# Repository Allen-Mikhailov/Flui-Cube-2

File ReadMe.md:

# An attempt to make a small cube that can simulate a fluid simulation on some led matricies

Using 788BS matrix for lights

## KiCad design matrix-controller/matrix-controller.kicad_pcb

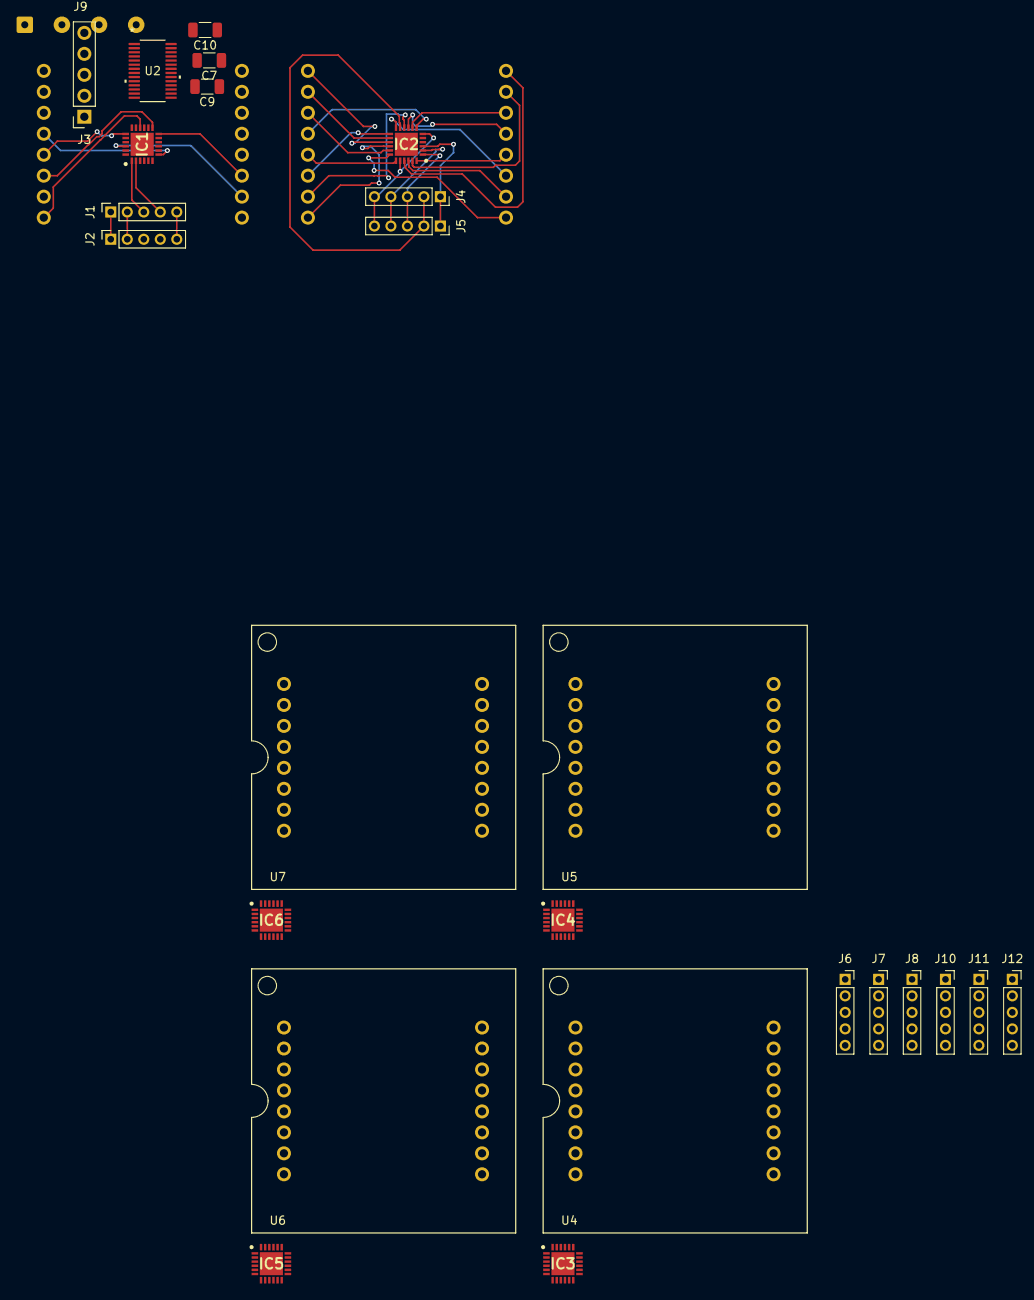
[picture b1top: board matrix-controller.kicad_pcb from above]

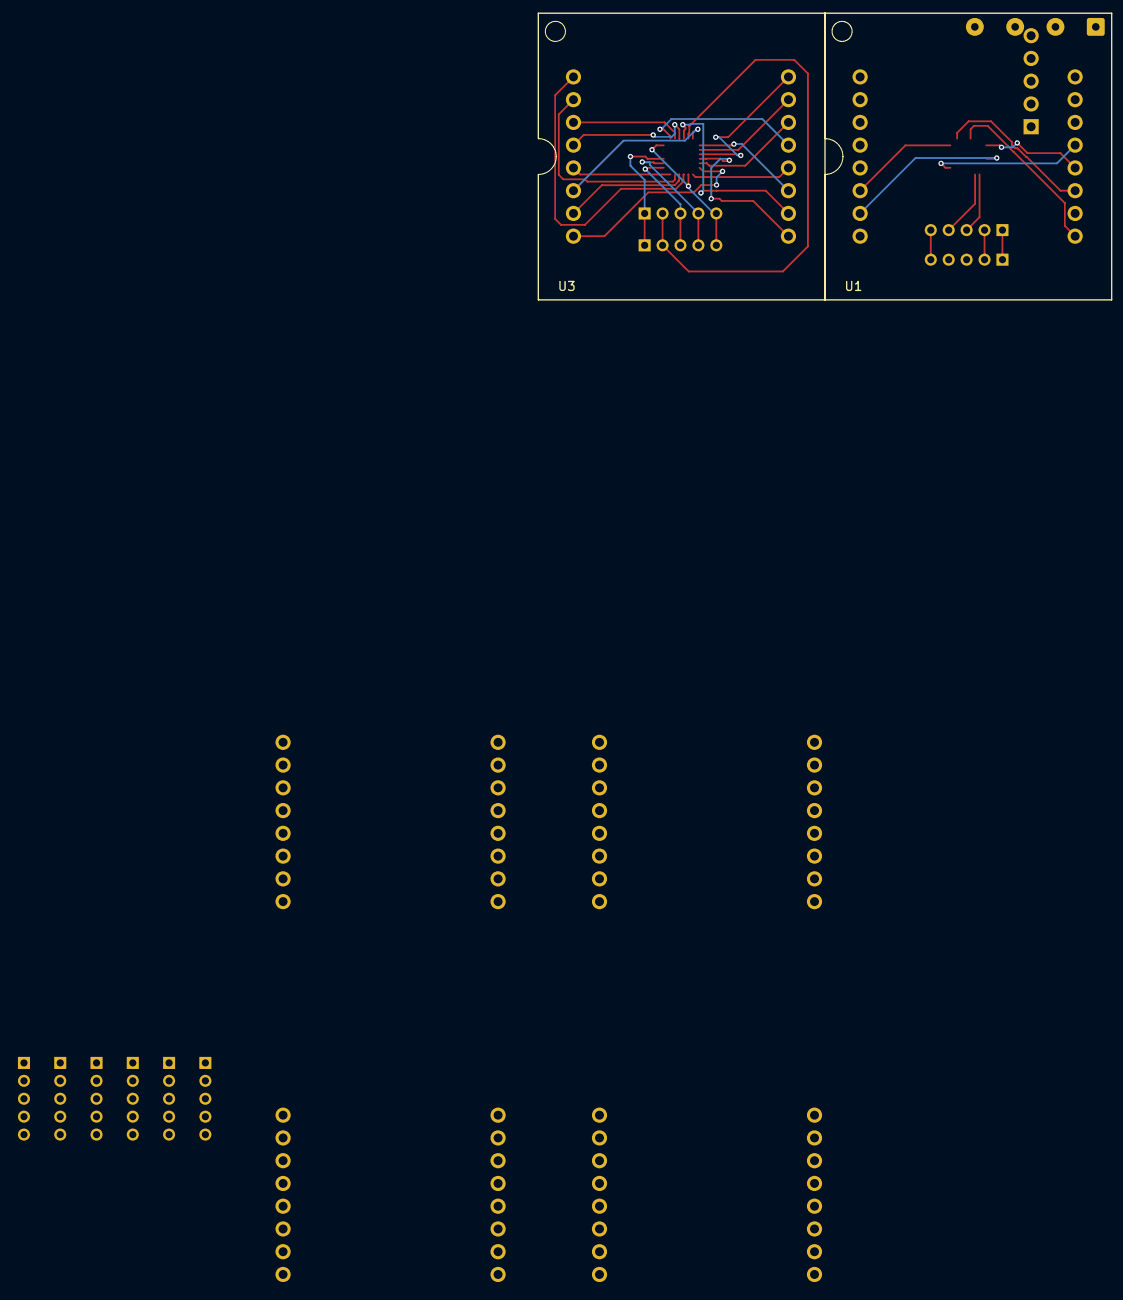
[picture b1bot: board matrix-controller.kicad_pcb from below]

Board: 2 copper layers, 28 parts (2 on the bottom side), 118 nets.

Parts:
C7: 10uF; C_1206_3216Metric
C9: 0.1uF; C_1206_3216Metric
C10: 0.47uF; C_1206_3216Metric
IC1, IC2, IC3, IC4, IC5, IC6: IS31FL3728-QFLS2-TR; QFN50P400X400X80-25N-D
J1: 1x05_Socket_Front; PinSocket_1x05_P2.00mm_Vertical
J2: 1x05_Socket_Back; PinSocket_1x05_P2.00mm_Vertical
J3: Conn_01x05_Pin; PinSocket_1x05_P2.54mm_Vertical
J4: 1x05_Socket_Front_Input; PinSocket_1x05_P2.00mm_Vertical
J5, J7: 1x05_Socket_Left; PinSocket_1x05_P2.00mm_Vertical
J6: 1x05_Socket_Left_Input; PinSocket_1x05_P2.00mm_Vertical
J8: 1x05_Socket_Top_Input; PinSocket_1x05_P2.00mm_Vertical
J9: Conn_01x04_Pin; SolderWire-0.25sqmm_1x04_P4.5mm_D0.65mm_OD2mm
J10: 1x05_SocketBack_Input; PinSocket_1x05_P2.00mm_Vertical
J11: 1x05_Socket_Right; PinSocket_1x05_P2.00mm_Vertical
J12: 1x05_Socket_Right_Input; PinSocket_1x05_P2.00mm_Vertical
U1, U3, U4, U5, U6, U7: 1088BS; LED_1088
U2: XMSM0G3507SDGS28R; VSSOP28_DGS_TEX

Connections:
/MatrixPlusDriver1/C1: IC2.24 (C1), U3.5 (C1)
/MatrixPlusDriver1/C2: IC2.23 (C2), U3.2 (C2)
/MatrixPlusDriver1/C3: IC2.22 (C3), U3.7 (C3)
/MatrixPlusDriver1/C4: IC2.21 (C4), U3.1 (C4)
/MatrixPlusDriver1/C5: IC2.19 (C5), U3.12 (C5)
/MatrixPlusDriver1/C6: IC2.18 (C6), U3.8 (C6)
/MatrixPlusDriver1/C7: IC2.17 (C7), U3.14 (C7)
/MatrixPlusDriver1/C8: IC2.16 (C8), U3.9 (C8)
/MatrixPlusDriver1/R1: IC2.7 (R1), U3.13 (R1)
/MatrixPlusDriver1/R2: IC2.8 (R2), U3.3 (R2)
/MatrixPlusDriver1/R3: IC2.9 (R3), U3.4 (R3)
/MatrixPlusDriver1/R4: IC2.10 (R4), U3.10 (R4)
/MatrixPlusDriver1/R5: IC2.12 (R5), U3.6 (R5)
/MatrixPlusDriver1/R6: IC2.13 (R6/C11), U3.11 (R6)
/MatrixPlusDriver1/R7: IC2.14 (R7/C10), U3.15 (R7)
/MatrixPlusDriver1/R8: IC2.15 (R8/C9), U3.16 (R8)
/MatrixPlusDriver2/C1: IC3.24 (C1), U4.5 (C1)
/MatrixPlusDriver2/C2: IC3.23 (C2), U4.2 (C2)
/MatrixPlusDriver2/C3: IC3.22 (C3), U4.7 (C3)
/MatrixPlusDriver2/C4: IC3.21 (C4), U4.1 (C4)
/MatrixPlusDriver2/C5: IC3.19 (C5), U4.12 (C5)
/MatrixPlusDriver2/C6: IC3.18 (C6), U4.8 (C6)
/MatrixPlusDriver2/C7: IC3.17 (C7), U4.14 (C7)
/MatrixPlusDriver2/C8: IC3.16 (C8), U4.9 (C8)
/MatrixPlusDriver2/R1: IC3.7 (R1), U4.13 (R1)
/MatrixPlusDriver2/R2: IC3.8 (R2), U4.3 (R2)
/MatrixPlusDriver2/R3: IC3.9 (R3), U4.4 (R3)
/MatrixPlusDriver2/R4: IC3.10 (R4), U4.10 (R4)
/MatrixPlusDriver2/R5: IC3.12 (R5), U4.6 (R5)
/MatrixPlusDriver2/R6: IC3.13 (R6/C11), U4.11 (R6)
/MatrixPlusDriver2/R7: IC3.14 (R7/C10), U4.15 (R7)
/MatrixPlusDriver2/R8: IC3.15 (R8/C9), U4.16 (R8)
/MatrixPlusDriver3/C1: IC4.24 (C1), U5.5 (C1)
/MatrixPlusDriver3/C2: IC4.23 (C2), U5.2 (C2)
/MatrixPlusDriver3/C3: IC4.22 (C3), U5.7 (C3)
/MatrixPlusDriver3/C4: IC4.21 (C4), U5.1 (C4)
/MatrixPlusDriver3/C5: IC4.19 (C5), U5.12 (C5)
/MatrixPlusDriver3/C6: IC4.18 (C6), U5.8 (C6)
/MatrixPlusDriver3/C7: IC4.17 (C7), U5.14 (C7)
/MatrixPlusDriver3/C8: IC4.16 (C8), U5.9 (C8)
/MatrixPlusDriver3/R1: IC4.7 (R1), U5.13 (R1)
/MatrixPlusDriver3/R2: IC4.8 (R2), U5.3 (R2)
/MatrixPlusDriver3/R3: IC4.9 (R3), U5.4 (R3)
/MatrixPlusDriver3/R4: IC4.10 (R4), U5.10 (R4)
/MatrixPlusDriver3/R5: IC4.12 (R5), U5.6 (R5)
/MatrixPlusDriver3/R6: IC4.13 (R6/C11), U5.11 (R6)
/MatrixPlusDriver3/R7: IC4.14 (R7/C10), U5.15 (R7)
/MatrixPlusDriver3/R8: IC4.15 (R8/C9), U5.16 (R8)
/MatrixPlusDriver4/C1: IC5.24 (C1), U6.5 (C1)
/MatrixPlusDriver4/C2: IC5.23 (C2), U6.2 (C2)
/MatrixPlusDriver4/C3: IC5.22 (C3), U6.7 (C3)
/MatrixPlusDriver4/C4: IC5.21 (C4), U6.1 (C4)
/MatrixPlusDriver4/C5: IC5.19 (C5), U6.12 (C5)
/MatrixPlusDriver4/C6: IC5.18 (C6), U6.8 (C6)
/MatrixPlusDriver4/C7: IC5.17 (C7), U6.14 (C7)
/MatrixPlusDriver4/C8: IC5.16 (C8), U6.9 (C8)
/MatrixPlusDriver4/R1: IC5.7 (R1), U6.13 (R1)
/MatrixPlusDriver4/R2: IC5.8 (R2), U6.3 (R2)
/MatrixPlusDriver4/R3: IC5.9 (R3), U6.4 (R3)
/MatrixPlusDriver4/R4: IC5.10 (R4), U6.10 (R4)
/MatrixPlusDriver4/R5: IC5.12 (R5), U6.6 (R5)
/MatrixPlusDriver4/R6: IC5.13 (R6/C11), U6.11 (R6)
/MatrixPlusDriver4/R7: IC5.14 (R7/C10), U6.15 (R7)
/MatrixPlusDriver4/R8: IC5.15 (R8/C9), U6.16 (R8)
/MatrixPlusDriver5/C1: IC6.24 (C1), U7.5 (C1)
/MatrixPlusDriver5/C2: IC6.23 (C2), U7.2 (C2)
/MatrixPlusDriver5/C3: IC6.22 (C3), U7.7 (C3)
/MatrixPlusDriver5/C4: IC6.21 (C4), U7.1 (C4)
/MatrixPlusDriver5/C5: IC6.19 (C5), U7.12 (C5)
/MatrixPlusDriver5/C6: IC6.18 (C6), U7.8 (C6)
/MatrixPlusDriver5/C7: IC6.17 (C7), U7.14 (C7)
/MatrixPlusDriver5/C8: IC6.16 (C8), U7.9 (C8)
/MatrixPlusDriver5/R1: IC6.7 (R1), U7.13 (R1)
/MatrixPlusDriver5/R2: IC6.8 (R2), U7.3 (R2)
/MatrixPlusDriver5/R3: IC6.9 (R3), U7.4 (R3)
/MatrixPlusDriver5/R4: IC6.10 (R4), U7.10 (R4)
/MatrixPlusDriver5/R5: IC6.12 (R5), U7.6 (R5)
/MatrixPlusDriver5/R6: IC6.13 (R6/C11), U7.11 (R6)
/MatrixPlusDriver5/R7: IC6.14 (R7/C10), U7.15 (R7)
/MatrixPlusDriver5/R8: IC6.15 (R8/C9), U7.16 (R8)
/MatrixPlusDriver/C1: IC1.24 (C1), U1.5 (C1)
/MatrixPlusDriver/C2: IC1.23 (C2), U1.2 (C2)
/MatrixPlusDriver/C3: IC1.22 (C3), U1.7 (C3)
/MatrixPlusDriver/C4: IC1.21 (C4), U1.1 (C4)
/MatrixPlusDriver/C5: IC1.19 (C5), U1.12 (C5)
/MatrixPlusDriver/C6: IC1.18 (C6), U1.8 (C6)
/MatrixPlusDriver/C7: IC1.17 (C7), U1.14 (C7)
/MatrixPlusDriver/C8: IC1.16 (C8), U1.9 (C8)
/MatrixPlusDriver/R1: IC1.7 (R1), U1.13 (R1)
/MatrixPlusDriver/R2: IC1.8 (R2), U1.3 (R2)
/MatrixPlusDriver/R3: IC1.9 (R3), U1.4 (R3)
/MatrixPlusDriver/R4: IC1.10 (R4), U1.10 (R4)
/MatrixPlusDriver/R5: IC1.12 (R5), U1.6 (R5)
/MatrixPlusDriver/R6: IC1.13 (R6/C11), U1.11 (R6)
/MatrixPlusDriver/R7: IC1.14 (R7/C10), U1.15 (R7)
/MatrixPlusDriver/R8: IC1.15 (R8/C9), U1.16 (R8)
GND: C7.2, C9.2, C10.1, IC1.6 (AD), IC1.20 (GND), IC2.20 (GND), IC3.20 (GND), IC4.20 (GND), IC5.6 (AD), IC5.20 (GND), IC6.20 (GND), J1.5, J2.5, J3.1, J4.5, J5.5, J6.5, J7.5, J8.5, J9.1, J10.5, J11.5, J12.5, U2.8 (VSS)
NRST: J3.3, U2.6 (NRST)
unnamed: C10.2, U2.3 (VCORE)
SCL0: IC1.2 (SCL), J1.4, U2.16 (PA11)
SCL0_B: IC5.2 (SCL), J10.4, J11.4
SCL0_F: IC2.2 (SCL), J4.4, J5.4, J9.2
SCL0_L: IC3.2 (SCL), IC4.6 (AD), J6.4, J7.4
SCL0_R: IC6.2 (SCL), J12.4
SCL0_T: IC4.2 (SCL), J8.4
SCL1: J2.4, U2.18 (PA15/A1_0)
SDA0: IC1.1 (SDA), J1.3, U2.15 (PA10/CLK_OUT)
SDA0_B: IC5.1 (SDA), J10.3, J11.3
SDA0_F: IC2.1 (SDA), J4.3, J5.3, J9.3
SDA0_L: IC3.1 (SDA), IC3.6 (AD), J6.3, J7.3
SDA0_R: IC6.1 (SDA), J12.3
SDA0_T: IC4.1 (SDA), J8.3
SDA1: J2.3, U2.19 (PA16/A1_1/FCC_IN)
SDB: IC1.3 (SDB), J1.1, J2.1
SWCLK: J3.5, U2.23 (PA20/SWCLK)
SWDIO: J3.4, U2.22 (PA19/SWDIO)
VCC: IC1.11 (VCC), IC2.3 (SDB), IC2.6 (AD), IC2.11 (VCC), IC3.3 (SDB), IC3.11 (VCC), IC4.3 (SDB), IC4.11 (VCC), IC5.3 (SDB), IC5.11 (VCC), IC6.3 (SDB), IC6.6 (AD), IC6.11 (VCC), J1.2, J2.2, J4.2, J5.2, J6.2, J7.2, J8.2, J9.4, J10.2, J11.2, J12.2
VLOGIC: C7.1, C9.1, J3.2, U2.7 (VDD)

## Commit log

2025-08-20 Project setup
2025-08-21 Initial Commit2
2025-09-27 Added Shift Registers controlling LED matrixies
2025-12-29 Base of the schematic is done, need to add IMU and regulator and finish the rest of the panels
2025-12-29 Schematic of other pannels mostly completed
2026-01-20 Updates to pcb. Switched to 4 wire connecions. Added IMU and usb C port footprints
